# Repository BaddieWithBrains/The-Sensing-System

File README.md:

# The-Sensing-System
Files for a micromouse project

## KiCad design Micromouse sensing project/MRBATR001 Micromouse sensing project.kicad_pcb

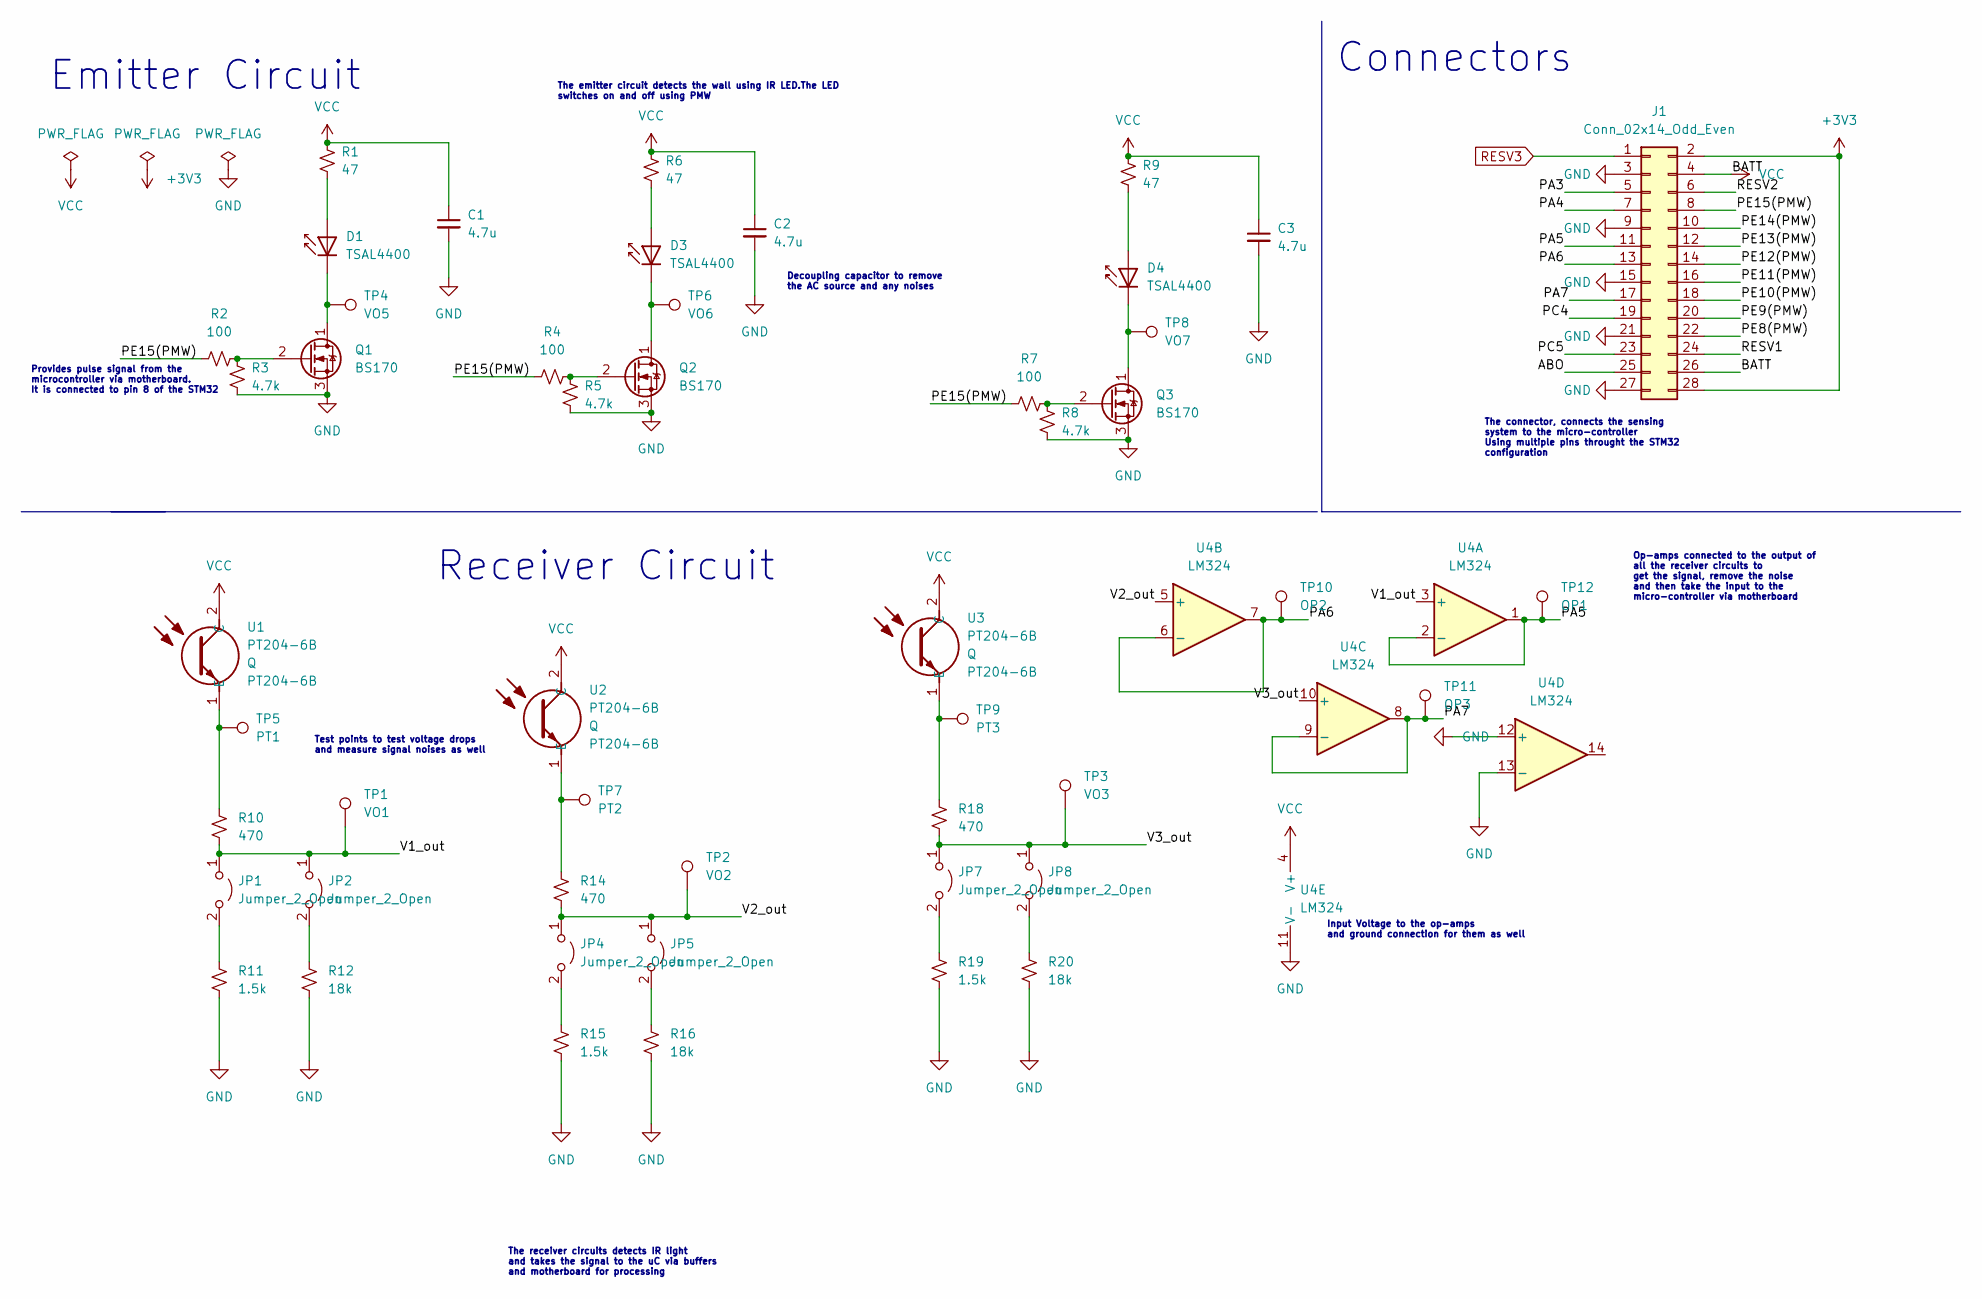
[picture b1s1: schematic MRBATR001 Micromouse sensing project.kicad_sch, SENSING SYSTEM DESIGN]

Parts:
C1, C2, C3: 4.7u; C_0805_2012Metric
D1, D3, D4: TSAL4400; LED_D3.0mm_Horizontal_O1.27mm_Z2.0mm_IRGrey
J1: Conn_02x14_Odd_Even; PinHeader_2x14_P2.54mm_Vertical
JP1, JP2, JP4, JP5, JP7, JP8: Jumper_2_Open; SolderJumper-2_P1.3mm_Bridged2Bar_RoundedPad1.0x1.5mm
Q1, Q2, Q3: BS170; TO-92_Inline
R1, R6, R9: 47; R_0805_2012Metric
R2, R4, R7: 100; R_0805_2012Metric
R3, R5, R8: 4.7k; R_0805_2012Metric
R10, R14, R18: 470; R_0805_2012Metric
R11, R15, R19: 1.5k; R_0805_2012Metric
R12, R16, R20: 18k; R_0805_2012Metric
TP1: VO1; TestPoint_2Pads_Pitch2.54mm_Drill0.8mm
TP2: VO2; TestPoint_2Pads_Pitch2.54mm_Drill0.8mm
TP3: VO3; TestPoint_2Pads_Pitch2.54mm_Drill0.8mm
TP4: VO5; TestPoint_2Pads_Pitch2.54mm_Drill0.8mm
TP5: PT1; TestPoint_2Pads_Pitch2.54mm_Drill0.8mm
TP6: VO6; TestPoint_2Pads_Pitch2.54mm_Drill0.8mm
TP7: PT2; TestPoint_2Pads_Pitch2.54mm_Drill0.8mm
TP8: VO7; TestPoint_2Pads_Pitch2.54mm_Drill0.8mm
TP9: PT3; TestPoint_2Pads_Pitch2.54mm_Drill0.8mm
TP10: OP2; TestPoint_2Pads_Pitch2.54mm_Drill0.8mm
TP11: OP3; TestPoint_2Pads_Pitch2.54mm_Drill0.8mm
TP12: OP1; TestPoint_2Pads_Pitch2.54mm_Drill0.8mm
U1, U2, U3: PT204-6B; LED_D3.0mm_Horizontal_O1.27mm_Z2.0mm_Clear; Manufacturer_Part_Number PT204-6B; Mouser Part Number N/A
U4: LM324; SOIC-14_3.9x8.7mm_P1.27mm

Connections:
+3V3: J1.2, J1.28
/ABO: J1.25
/PA3: J1.5
/PA4: J1.7
/PA5: J1.11, TP12.1, U4.1, U4.2 (-)
/PA6: J1.13, TP10.1, U4.6 (-), U4.7
/PA7: J1.17, TP11.1, U4.8, U4.9 (-)
/PC4: J1.19
/PC5: J1.23
/PE8(PMW): J1.22
/PE9(PMW): J1.20
/PE10(PMW): J1.18
/PE11(PMW): J1.16
/PE12(PMW): J1.14
/PE13(PMW): J1.12
/PE14(PMW): J1.10
/PE15(PMW): J1.8, R2.1, R4.1, R7.1
/RESV1: J1.24
/RESV2: J1.6
/V1_out: JP1.1 (A), JP2.1 (A), R10.2, TP1.1, U4.3 (+)
/V2_out: JP4.1 (A), JP5.1 (A), R14.2, TP2.1, U4.5 (+)
/V3_out: JP7.1 (A), JP8.1 (A), R18.2, TP3.1, U4.10 (+)
GND: C1.2, C2.2, C3.2, J1.3, J1.9, J1.15, J1.21, J1.27, Q1.3 (S), Q2.3 (S), Q3.3 (S), R3.2, R5.2, R8.2, R11.2, R12.2, R15.2, R16.2, R19.2, R20.2, U4.11 (V-), U4.12 (+), U4.13 (-)
unnamed: D1.1 (K), Q1.1 (D), TP4.1
unnamed: D1.2 (A), R1.2
unnamed: D3.1 (K), Q2.1 (D), TP6.1
unnamed: D3.2 (A), R6.2
unnamed: D4.1 (K), Q3.1 (D), TP8.1
unnamed: D4.2 (A), R9.2
unnamed: JP1.2 (B), R11.1
unnamed: JP2.2 (B), R12.1
unnamed: JP4.2 (B), R15.1
unnamed: JP5.2 (B), R16.1
unnamed: JP7.2 (B), R19.1
unnamed: JP8.2 (B), R20.1
unnamed: Q1.2 (G), R2.2, R3.1
unnamed: Q2.2 (G), R4.2, R5.1
unnamed: Q3.2 (G), R7.2, R8.1
unnamed: R10.1, TP5.1, U1.1 (E)
unnamed: R14.1, TP7.1, U2.1 (E)
unnamed: R18.1, TP9.1, U3.1 (E)
RESV3: J1.1
VCC: C1.1, C2.1, C3.1, J1.4, J1.26, R1.1, R6.1, R9.1, U1.2 (C), U2.2 (C), U3.2 (C), U4.4 (V+)

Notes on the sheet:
Provides pulse signal from the microcontroller via motherboard. It is connected to pin 8 of the STM32
The receiver circuits detects IR light and takes the signal to the uC via buffers and motherboard for processing
Test points to test voltage drops and measure signal noises as well
Emitter Circuit
Decoupling capacitor to remove the AC source and any noises
Op-amps connected to the output of all the receiver circuits to get the signal, remove the noise and then take the input to the micro-controller via motherboard
Receiver Circuit
The emitter circuit detects the wall using IR LED.The LED switches on and off using PMW
Input Voltage to the op-amps and ground connection for them as well
Connectors
The connector, connects the sensing system to the micro-controller Using multiple pins throught the STM32 configuration

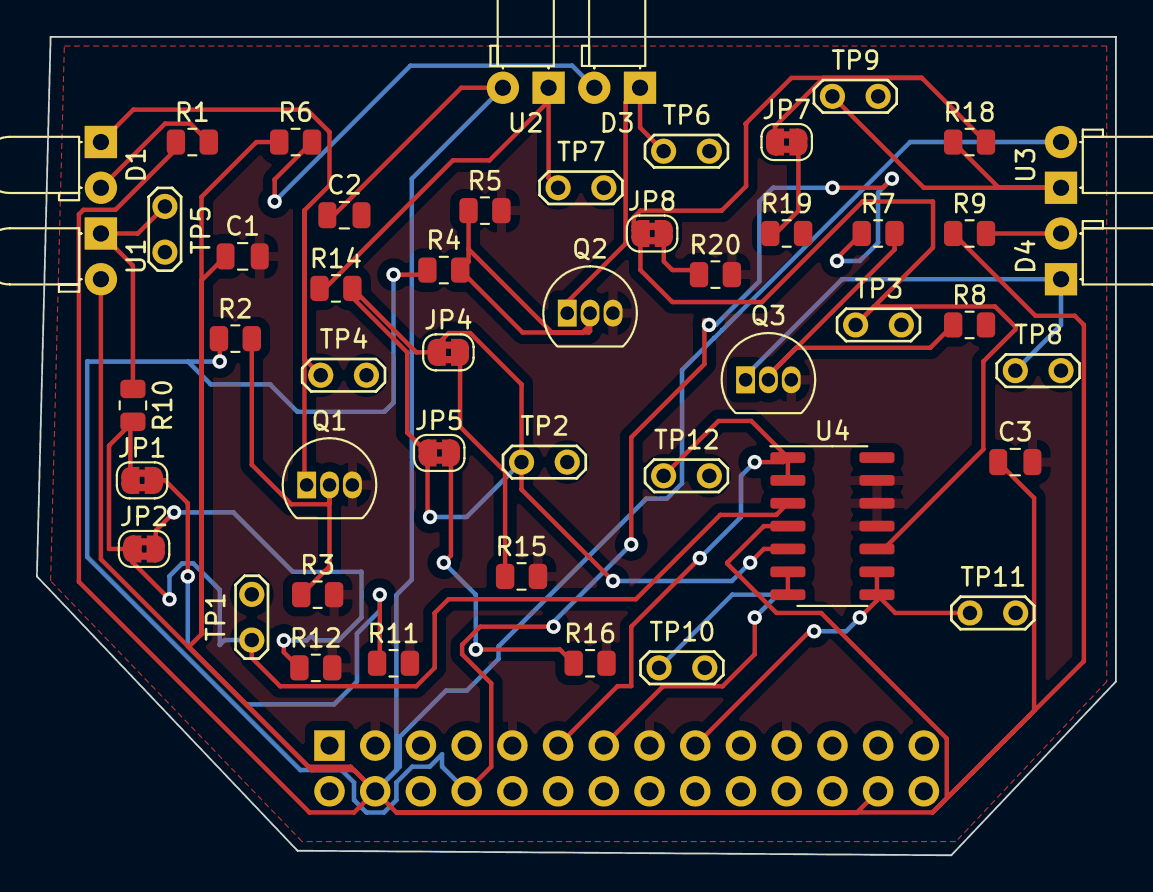
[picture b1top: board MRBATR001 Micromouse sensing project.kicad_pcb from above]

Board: 2 copper layers, 59.9 x 45.5 mm, 50 parts (1 on the bottom side), 28 nets.
